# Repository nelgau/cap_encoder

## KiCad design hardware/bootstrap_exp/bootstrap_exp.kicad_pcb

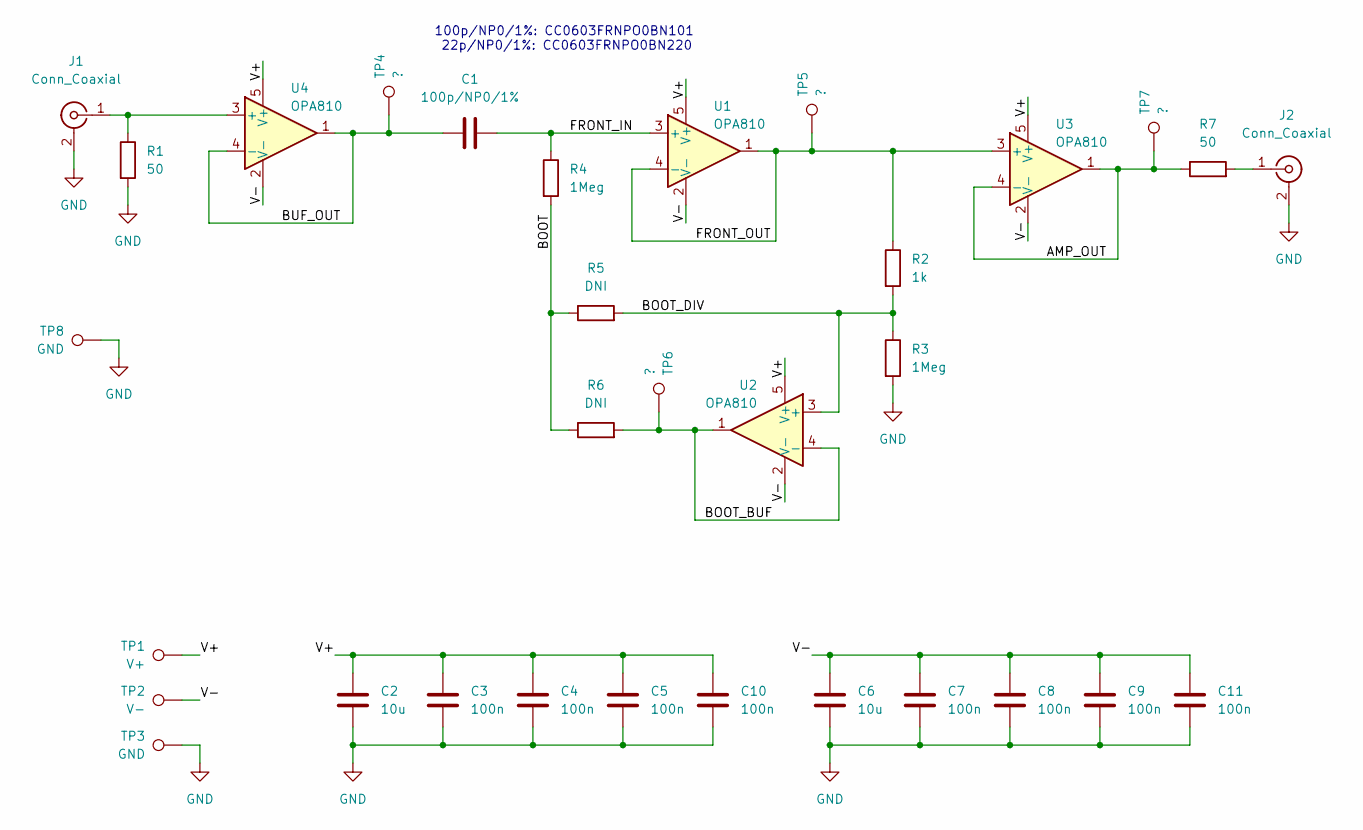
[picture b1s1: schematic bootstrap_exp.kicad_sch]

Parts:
C1: 100p/NP0/1%; C_0603_1608Metric; MPN CC0603FRNPO0BN101
C2, C6: 10u; CP_EIA-3528-12_Kemet-T; MPN T491B106K025AT
C3, C4, C5, C7, C8, C9, C10, C11: 100n; C_0603_1608Metric; MPN CL10B104KB8NNNC
J1, J2: Conn_Coaxial; SMA_Samtec_SMA-J-P-X-ST-EM1_EdgeMount
R1, R7: 50; R_0805_2012Metric; MPN ERA-6AEB49R9V
R2: 1k; R_0603_1608Metric; MPN RC0603FR-071KL
R3, R4: 1Meg; R_0603_1608Metric; MPN RC0603FR-071ML
R5, R6: DNI; R_0603_1608Metric; MPN RC0603FR-070RL
TP1: V+; TestPoint_Keystone_5005-5009_Compact; MPN 5007
TP2: V-; TestPoint_Keystone_5005-5009_Compact; MPN 5007
TP3, TP8: GND; TestPoint_Keystone_5005-5009_Compact; MPN 5007
TP4, TP5, TP6, TP7: ?; TestPoint_Keystone_5005-5009_Compact; MPN 5007
U1, U2, U3, U4: OPA810; SOT-353_SC-70-5; MPN OPA810IDCKR

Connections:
/AMP_OUT: R7.1, TP7.1, U3.1, U3.4 (-)
/BOOT: R4.2, R5.1, R6.1
/BOOT_BUF: R6.2, TP6.1, U2.1, U2.4 (-)
/BOOT_DIV: R2.2, R3.1, R5.2, U2.3 (+)
/BUF_OUT: C1.2, TP4.1, U4.1, U4.4 (-)
/FRONT_IN: C1.1, R4.1, U1.3 (+)
/FRONT_OUT: R2.1, TP5.1, U1.1, U1.4 (-), U3.3 (+)
/V+: C2.1, C3.1, C4.1, C5.1, C10.1, TP1.1, U1.5 (V+), U2.5 (V+), U3.5 (V+), U4.5 (V+)
/V-: C6.1, C7.1, C8.1, C9.1, C11.1, TP2.1, U1.2 (V-), U2.2 (V-), U3.2 (V-), U4.2 (V-)
GND: C2.2, C3.2, C4.2, C5.2, C6.2, C7.2, C8.2, C9.2, C10.2, C11.2, J1.2 (Ext), J2.2 (Ext), R1.2, R3.2, TP3.1, TP8.1
unnamed: J1.1 (In), R1.1, U4.3 (+)
unnamed: J2.1 (In), R7.2

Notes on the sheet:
100p/NP0/1%: CC0603FRNPO0BN101 22p/NP0/1%: CC0603FRNPO0BN220

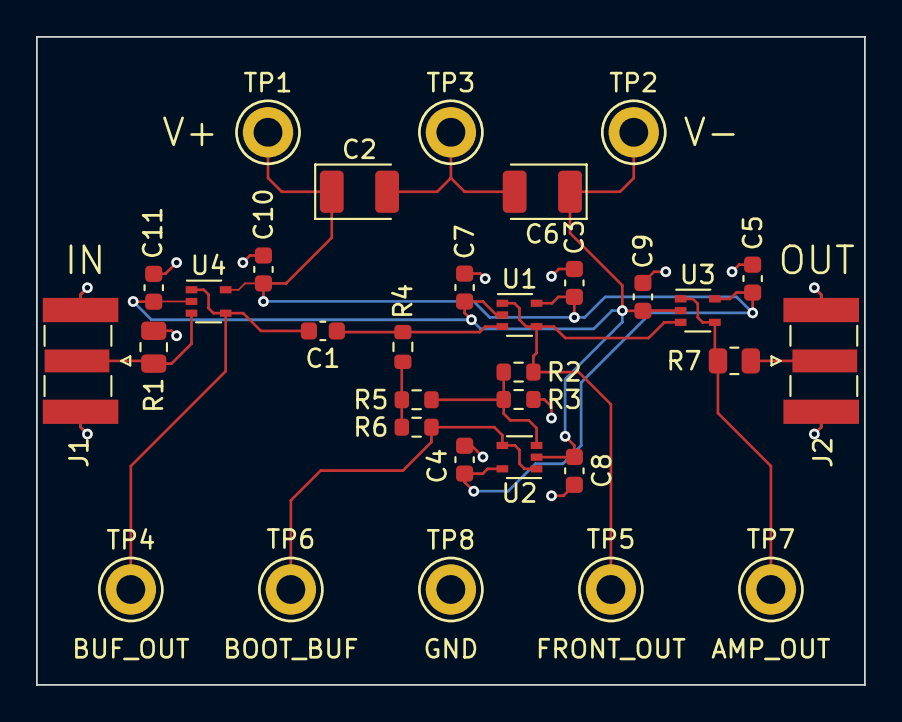
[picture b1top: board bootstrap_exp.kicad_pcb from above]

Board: 4 copper layers, 46.0 x 36.0 mm, 32 parts (0 on the bottom side), 12 nets.

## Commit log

2022-03-09 Update gitignore to include v6 autosaves
2022-03-09 Add decoupling and test points
2022-03-09 Assign initial footprints for layout checks
2022-03-09 Initial PCB layout for evaluation
2022-03-09 Setup physical stackup and design rules
2022-03-11 Remove sensitive pad and replace headers with jumper resistors
2022-03-11 Assign missing footprints
2022-03-11 Adjust layout for simplified design
2022-03-11 Remove test point for bootstrapped high-Z node
2022-03-11 Assign names to nets
2022-04-09 Add input buffer
2022-04-09 Finish routing
2022-04-09 Specify dielectric for input coupling capacitance
2022-04-10 Update OPA810 footprint to SC-70-5, workaround for shortages
2022-04-10 Reroute design for new amplifier footprint
2022-04-11 Move SMA connectors to fix edge clearance violations
2022-04-12 Specify MPN and source for every component
2022-04-12 Specify source for resistors
2022-04-13 Adjust zone clearance to fab minimum
2022-04-13 Make edge cut extents an integer for width and height
2022-04-13 Nudge connectors closer to new edge
2022-04-13 Disable paste on SMA connector pads (not in library)
2022-04-13 Output gerbers and drill files for RevA
2022-07-13 Import old encoder geometry code
2022-08-22 Add generator plugin skeleton
2022-08-22 Add geomgen package
2022-08-23 Call out to geomgen via poetry
2022-08-24 Plotting zones via plugin and geomgen
